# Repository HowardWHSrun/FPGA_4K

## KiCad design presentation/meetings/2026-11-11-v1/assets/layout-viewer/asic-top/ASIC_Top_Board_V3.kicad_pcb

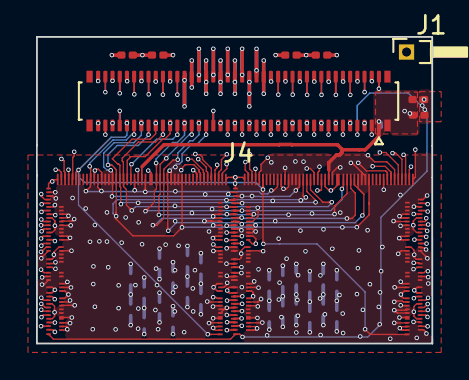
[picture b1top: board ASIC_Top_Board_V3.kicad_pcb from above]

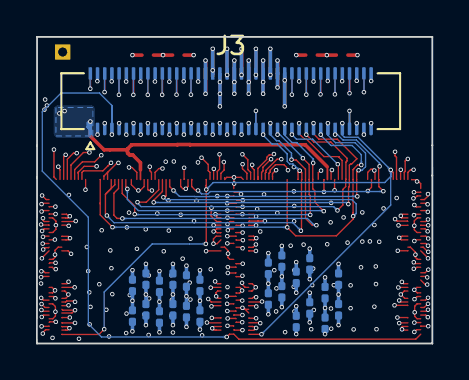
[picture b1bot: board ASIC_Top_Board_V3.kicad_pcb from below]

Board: 10 copper layers, 22.0 x 17.0 mm, 35 parts (25 on the bottom side), 78 nets.

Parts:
C1, C2, C4, C5, C6, C7, C14, C18, C19, C25, C26, C33, C34, C41, C42, C46, C48, C50, C51, C52, C53, C54, C55, C56, C57, C58, C59, C60, C61, C62: C_Small_US; C_0201_0603Metric
J1: Conn_01x01_Pin; PinHeader_1x01_P1.00mm_Horizontal
J3: Conn_02x40_Odd_Even; Hirose_DF40C-80DS-0.4V_2x40_P0.4mm
J4: Conn_02x40_Odd_Even; Hirose_DF40C-80DP-0.4V_2x40-1MP_P0.4mm
U01_BCD1, U01_BCD2: *; U01_BCD_OFF_CHIP

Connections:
/AC_IN: J3.69, J4.69, U01_BCD1.AC_IN, U01_BCD2.AC_IN
/AGND: C1.2, C2.2, C4.2, C5.2, C6.2, C18.2, C19.2, C25.2, C26.2, C33.2, C34.2, C41.2, C42.2, C46.2, C48.2, C50.2, C51.2, C52.2, C53.2, C54.2, C55.2, C56.2, C57.2, C58.2, C59.2, C60.2, J1.1 (Pin_1_1), J3.42, J3.44, J4.42, J4.44, U01_BCD1.AGND2, U01_BCD1.AGND_1, U01_BCD1.LAGND_1, U01_BCD1.LAGND_2, U01_BCD1.LAGND_3, U01_BCD1.LAGND_4, U01_BCD1.LAGND_5, U01_BCD1.LAGND_6, U01_BCD1.LAGND_7, U01_BCD1.LAGND_8, U01_BCD1.LAGND_9, U01_BCD1.LAGND_10, U01_BCD1.LAGND_11, U01_BCD1.LAGND_12, U01_BCD1.LAGND_13, U01_BCD1.LAGND_14, U01_BCD1.LAGND_15, U01_BCD1.LREF_GND1, U01_BCD1.LREF_GND2, U01_BCD1.LREF_GND3, U01_BCD1.LREF_GND4, U01_BCD1.RAGND_1, U01_BCD1.RAGND_2, U01_BCD1.RAGND_3, U01_BCD1.RAGND_4, U01_BCD1.RAGND_5, U01_BCD1.RAGND_6, U01_BCD1.RAGND_7, U01_BCD1.RAGND_8, U01_BCD1.RAGND_9, U01_BCD1.RAGND_10, U01_BCD1.RAGND_11, U01_BCD1.RAGND_12, U01_BCD1.RAGND_13, U01_BCD1.RAGND_14, U01_BCD1.RAGND_15, U01_BCD1.REF_1, U01_BCD1.REF_2, U01_BCD1.REF_3, U01_BCD1.REF_4, U01_BCD1.RREF_GND1, U01_BCD1.RREF_GND2, U01_BCD1.RREF_GND3, U01_BCD1.RREF_GND4, U01_BCD2.AGND2, U01_BCD2.AGND_1, U01_BCD2.LAGND_1, U01_BCD2.LAGND_2, U01_BCD2.LAGND_3, U01_BCD2.LAGND_4, U01_BCD2.LAGND_5, U01_BCD2.LAGND_6, U01_BCD2.LAGND_7, U01_BCD2.LAGND_8, U01_BCD2.LAGND_9, U01_BCD2.LAGND_10, U01_BCD2.LAGND_11, U01_BCD2.LAGND_12, U01_BCD2.LAGND_13, U01_BCD2.LAGND_14, U01_BCD2.LAGND_15, U01_BCD2.LREF_GND1, U01_BCD2.LREF_GND2, U01_BCD2.LREF_GND3, U01_BCD2.LREF_GND4, U01_BCD2.RAGND_1, U01_BCD2.RAGND_2, U01_BCD2.RAGND_3, U01_BCD2.RAGND_4, U01_BCD2.RAGND_5, U01_BCD2.RAGND_6, U01_BCD2.RAGND_7, U01_BCD2.RAGND_8, U01_BCD2.RAGND_9, U01_BCD2.RAGND_10, U01_BCD2.RAGND_11, U01_BCD2.RAGND_12, U01_BCD2.RAGND_13, U01_BCD2.RAGND_14, U01_BCD2.RAGND_15, U01_BCD2.REF_1, U01_BCD2.REF_2, U01_BCD2.REF_3, U01_BCD2.REF_4, U01_BCD2.RREF_GND1, U01_BCD2.RREF_GND2, U01_BCD2.RREF_GND3, U01_BCD2.RREF_GND4
/CHIP_RESET: J3.71, J4.71, U01_BCD1.RRST_DIGITAL, U01_BCD1.RST_DRIVER, U01_BCD2.RRST_DIGITAL, U01_BCD2.RST_DRIVER
/CLK32MHZ: J3.45, J4.45
/CLK32MHZ(2): J3.19, J4.19
/CLKH: J3.7, J4.7, U01_BCD1.CLKH, U01_BCD2.CLKH
/D<1>: J3.79, J4.79
/D<1>(2): J3.33, J4.33
/D<2>: J3.77, J4.77
/D<2>(2): J3.31, J4.31
/D<3>: J3.75, J4.75
/D<3>(2): J3.29, J4.29
/D<4>: J3.73, J4.73
/D<4>(2): J3.27, J4.27
/D<5>: J3.43, J4.43
/D<5>(2): J3.17, J4.17
/D<6>: J3.41, J4.41
/D<6>(2): J3.15, J4.15
/D<7>: J3.39, J4.39
/D<7>(2): J3.13, J4.13
/D<8>: J3.37, J4.37
/D<8>(2): J3.11, J4.11
/DGND: C7.2, C14.2, C61.2, C62.2, J3.46, J3.48, J4.46, J4.48, U01_BCD1.DGND1, U01_BCD1.DGND2, U01_BCD1.DGND3, U01_BCD1.DGND4, U01_BCD1.EN_LDO, U01_BCD1.LDGND_1, U01_BCD1.LDGND_2, U01_BCD1.LDGND_3, U01_BCD1.LDGND_4, U01_BCD1.LDGND_5, U01_BCD1.LDGND_6, U01_BCD1.LDGND_7, U01_BCD1.LDGND_8, U01_BCD1.LDGND_9, U01_BCD1.LDGND_10, U01_BCD1.LDGND_11, U01_BCD1.LDGND_12, U01_BCD1.LDGND_13, U01_BCD1.RDGND_1, U01_BCD1.RDGND_2, U01_BCD1.RDGND_3, U01_BCD1.RDGND_4, U01_BCD1.RDGND_5, U01_BCD1.RDGND_6, U01_BCD1.RDGND_7, U01_BCD1.RDGND_8, U01_BCD1.RDGND_9, U01_BCD1.RDGND_10, U01_BCD1.RDGND_11, U01_BCD1.RDGND_12, U01_BCD1.RDGND_13, U01_BCD2.DGND1, U01_BCD2.DGND2, U01_BCD2.DGND3, U01_BCD2.DGND4, U01_BCD2.EN_LDO, U01_BCD2.LDGND_1, U01_BCD2.LDGND_2, U01_BCD2.LDGND_3, U01_BCD2.LDGND_4, U01_BCD2.LDGND_5, U01_BCD2.LDGND_6, U01_BCD2.LDGND_7, U01_BCD2.LDGND_8, U01_BCD2.LDGND_9, U01_BCD2.LDGND_10, U01_BCD2.LDGND_11, U01_BCD2.LDGND_12, U01_BCD2.LDGND_13, U01_BCD2.RDGND_1, U01_BCD2.RDGND_2, U01_BCD2.RDGND_3, U01_BCD2.RDGND_4, U01_BCD2.RDGND_5, U01_BCD2.RDGND_6, U01_BCD2.RDGND_7, U01_BCD2.RDGND_8, U01_BCD2.RDGND_9, U01_BCD2.RDGND_10, U01_BCD2.RDGND_11, U01_BCD2.RDGND_12, U01_BCD2.RDGND_13
/DISC_OUT: J3.5, J4.5
/DISC_OUT(2): J3.3, J4.3
/DVDD: C7.1, C14.1, C61.1, C62.1, J3.34, J4.34, U01_BCD1.CGEN_RST, U01_BCD1.LDVDD_B1, U01_BCD1.LDVDD_B2, U01_BCD1.LDVDD_B3, U01_BCD1.LDVDD_T1, U01_BCD1.LDVDD_T2, U01_BCD1.LDVDD_T3, U01_BCD1.RDVDD_B1, U01_BCD1.RDVDD_B2, U01_BCD1.RDVDD_B3, U01_BCD1.RDVDD_T1, U01_BCD1.RDVDD_T2, U01_BCD1.RDVDD_T3, U01_BCD1.SPI_LDO_O, U01_BCD1.SPI_LDO_P, U01_BCD1.SPI_LDO_P1, U01_BCD1.SPI_LDO_P2, U01_BCD2.CGEN_RST, U01_BCD2.LDVDD_B1, U01_BCD2.LDVDD_B2, U01_BCD2.LDVDD_B3, U01_BCD2.LDVDD_T1, U01_BCD2.LDVDD_T2, U01_BCD2.LDVDD_T3, U01_BCD2.RDVDD_B1, U01_BCD2.RDVDD_B2, U01_BCD2.RDVDD_B3, U01_BCD2.RDVDD_T1, U01_BCD2.RDVDD_T2, U01_BCD2.RDVDD_T3, U01_BCD2.SPI_LDO_O, U01_BCD2.SPI_LDO_P, U01_BCD2.SPI_LDO_P1, U01_BCD2.SPI_LDO_P2
/FE_RESET: J3.65, J4.65, U01_BCD1.RST_FEL, U01_BCD1.RST_FER, U01_BCD2.RST_FEL, U01_BCD2.RST_FER
/IMP_TEST: J3.67, J4.67, U01_BCD1.IMP_TST, U01_BCD2.IMP_TST
/READ: J3.35, J4.35
/READ(2): J3.9, J4.9
/REF_VCM: C5.1, C46.1, C57.1, C58.1, J3.40, J4.40, U01_BCD1.LREF_VCM1, U01_BCD1.LREF_VCM2, U01_BCD1.LREF_VCM3, U01_BCD1.LREF_VCM4, U01_BCD1.RREF_VCM1, U01_BCD1.RREF_VCM2, U01_BCD1.RREF_VCM3, U01_BCD1.RREF_VCM4, U01_BCD1.VCM, U01_BCD2.LREF_VCM1, U01_BCD2.LREF_VCM2, U01_BCD2.LREF_VCM3, U01_BCD2.LREF_VCM4, U01_BCD2.RREF_VCM1, U01_BCD2.RREF_VCM2, U01_BCD2.RREF_VCM3, U01_BCD2.RREF_VCM4, U01_BCD2.VCM
/REF_VDD: C2.1, C33.1, C55.1, C56.1, J3.52, J4.52, U01_BCD1.LREF_VDD1, U01_BCD1.LREF_VDD2, U01_BCD1.LREF_VDD3, U01_BCD1.LREF_VDD4, U01_BCD1.RREF_VDD1, U01_BCD1.RREF_VDD2, U01_BCD1.RREF_VDD3, U01_BCD1.RREF_VDD4, U01_BCD2.LREF_VDD1, U01_BCD2.LREF_VDD2, U01_BCD2.LREF_VDD3, U01_BCD2.LREF_VDD4, U01_BCD2.RREF_VDD1, U01_BCD2.RREF_VDD2, U01_BCD2.RREF_VDD3, U01_BCD2.RREF_VDD4
/SPARE_P2: J3.2, J4.2
/SPARE_P4: J3.4, J4.4
/SPARE_P6: J3.6, J4.6
/SPARE_P8: J3.8, J4.8
/SPARE_P24: J3.24, J4.24
/SPARE_P58: J3.58, J4.58
/SPI_CLK: J3.63, J4.63, U01_BCD1.SPI_CLK, U01_BCD2.SPI_CLK
/SPI_DINL: J3.59, J4.59, U01_BCD1.SPI_DINL
/SPI_DINL(2): J3.25, J4.25, U01_BCD2.SPI_DINL
/SPI_DINR: J3.57, J4.57, U01_BCD1.SPI_DINR
/SPI_DINR(2): J3.23, J4.23, U01_BCD2.SPI_DINR
/SPI_LATCH: J3.61, J4.61, U01_BCD1.SPI_LATCH, U01_BCD2.SPI_LATCH
/STIM_CHB: J3.49, J4.49, U01_BCD1.FPGA_CHBL, U01_BCD1.FPGA_CHBR, U01_BCD2.FPGA_CHBL, U01_BCD2.FPGA_CHBR
/STIM_CLK: J3.53, J4.53, U01_BCD1.FPGA_CLK, U01_BCD2.FPGA_CLK
/STIM_EN: J3.51, J4.51, U01_BCD1.FPGA_EN, U01_BCD2.FPGA_EN
/STIM_START: J3.55, J4.55, U01_BCD1.FPGA_START, U01_BCD2.FPGA_START
/SYNC: J3.47, J4.47
/SYNC(2): J3.21, J4.21
/T_CLK32MHZ: J3.70, J4.70, U01_BCD1.CLK32MHZ
/T_CLK32MHZ(2): J3.20, J4.20, U01_BCD2.CLK32MHZ
/T_D<1>: J3.80, J4.80, U01_BCD1.DATAL<4>
/T_D<1>(2): J3.32, J4.32, U01_BCD2.DATAL<4>
/T_D<2>: J3.78, J4.78, U01_BCD1.DATAL<3>
/T_D<2>(2): J3.30, J4.30, U01_BCD2.DATAL<3>
/T_D<3>: J3.76, J4.76, U01_BCD1.DATAL<2>
/T_D<3>(2): J3.28, J4.28, U01_BCD2.DATAL<2>
/T_D<4>: J3.74, J4.74, U01_BCD1.DATAL<1>
/T_D<4>(2): J3.26, J4.26, U01_BCD2.DATAL<1>
/T_D<5>: J3.68, J4.68, U01_BCD1.DATAR<4>
/T_D<5>(2): J3.18, J4.18, U01_BCD2.DATAR<4>
/T_D<6>: J3.66, J4.66, U01_BCD1.DATAR<3>
/T_D<6>(2): J3.16, J4.16, U01_BCD2.DATAR<3>
/T_D<7>: J3.64, J4.64, U01_BCD1.DATAR<2>
/T_D<7>(2): J3.14, J4.14, U01_BCD2.DATAR<2>
/T_D<8>: J3.62, J4.62, U01_BCD1.DATAR<1>
/T_D<8>(2): J3.12, J4.12, U01_BCD2.DATAR<1>
/T_READ: J3.60, J4.60, U01_BCD1.READ
/T_READ(2): J3.10, J4.10, U01_BCD2.READ
/T_SYNC: J3.72, J4.72, U01_BCD1.SYNC
/T_SYNC(2): J3.22, J4.22, U01_BCD2.SYNC
/VDD10: C18.1, C19.1, J3.36, J4.36, U01_BCD1.P10_L, U01_BCD1.P10_R, U01_BCD2.P10_L, U01_BCD2.P10_R
/VDD_ADC: C1.1, C34.1, C53.1, C54.1, J3.56, J4.56, U01_BCD1.LVDD_ADC1, U01_BCD1.LVDD_ADC2, U01_BCD1.LVDD_ADC3, U01_BCD1.LVDD_ADC4, U01_BCD1.LVDD_ADC5, U01_BCD1.RVDD_ADC1, U01_BCD1.RVDD_ADC2, U01_BCD1.RVDD_ADC3, U01_BCD1.RVDD_ADC4, U01_BCD1.RVDD_ADC5, U01_BCD2.LVDD_ADC1, U01_BCD2.LVDD_ADC2, U01_BCD2.LVDD_ADC3, U01_BCD2.LVDD_ADC4, U01_BCD2.LVDD_ADC5, U01_BCD2.RVDD_ADC1, U01_BCD2.RVDD_ADC2, U01_BCD2.RVDD_ADC3, U01_BCD2.RVDD_ADC4, U01_BCD2.RVDD_ADC5
/VDD_CGEN: C6.1, C50.1, J3.1, J4.1, U01_BCD1.VDD_CGEN, U01_BCD2.VDD_CGEN
/VDD_DRIVER: C41.1, C42.1, C59.1, C60.1, J3.38, J4.38, U01_BCD1.LVDD_DRIVER1, U01_BCD1.LVDD_DRIVER2, U01_BCD1.LVDD_DRIVER3, U01_BCD1.LVDD_DRIVER4, U01_BCD1.LVDD_DRIVER5, U01_BCD1.RVDD_DRIVER1, U01_BCD1.RVDD_DRIVER2, U01_BCD1.RVDD_DRIVER3, U01_BCD1.RVDD_DRIVER4, U01_BCD1.RVDD_DRIVER5, U01_BCD2.LVDD_DRIVER1, U01_BCD2.LVDD_DRIVER2, U01_BCD2.LVDD_DRIVER3, U01_BCD2.LVDD_DRIVER4, U01_BCD2.LVDD_DRIVER5, U01_BCD2.RVDD_DRIVER1, U01_BCD2.RVDD_DRIVER2, U01_BCD2.RVDD_DRIVER3, U01_BCD2.RVDD_DRIVER4, U01_BCD2.RVDD_DRIVER5
/VDD_FE: C4.1, C48.1, C51.1, C52.1, J3.50, J4.50, U01_BCD1.LVDD_FE1, U01_BCD1.LVDD_FE2, U01_BCD1.LVDD_FE3, U01_BCD1.LVDD_FE4, U01_BCD1.RVDD_FE1, U01_BCD1.RVDD_FE2, U01_BCD1.RVDD_FE3, U01_BCD1.RVDD_FE4, U01_BCD2.LVDD_FE1, U01_BCD2.LVDD_FE2, U01_BCD2.LVDD_FE3, U01_BCD2.LVDD_FE4, U01_BCD2.RVDD_FE1, U01_BCD2.RVDD_FE2, U01_BCD2.RVDD_FE3, U01_BCD2.RVDD_FE4
/VSS10: C25.1, C26.1, J3.54, J4.54, U01_BCD1.M10_L, U01_BCD1.M10_R, U01_BCD2.M10_L, U01_BCD2.M10_R

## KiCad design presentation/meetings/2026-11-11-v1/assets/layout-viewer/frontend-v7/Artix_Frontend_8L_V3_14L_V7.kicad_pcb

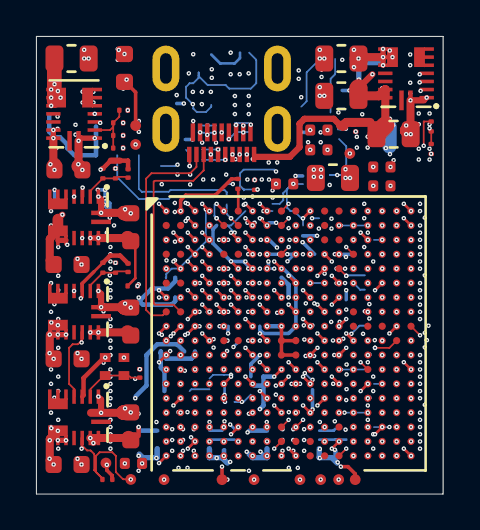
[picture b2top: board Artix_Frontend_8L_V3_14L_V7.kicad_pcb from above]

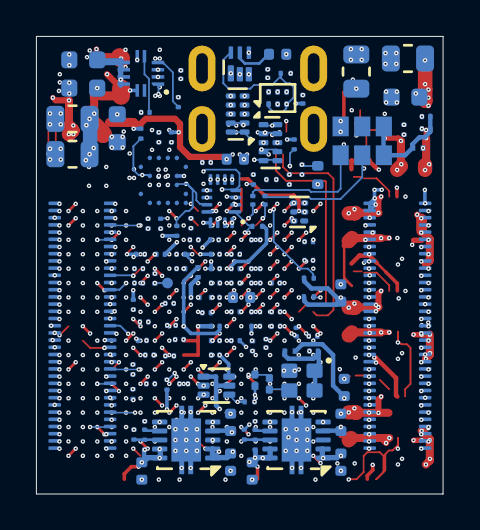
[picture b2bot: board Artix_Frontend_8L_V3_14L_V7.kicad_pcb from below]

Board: 14 copper layers, 22.6 x 25.4 mm, 185 parts (126 on the bottom side), 189 nets.

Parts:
C1, C2, C12, C13, C21, C22, C85, C86: 22uF; C_0603_1608Metric
C3, C14, C23, C87: 22pF; C_0201_GRM03_Murata_0p22Gap
C4, C89: 100uF; C_0805_2012Metric
C5, C6, C25, C36, C37, C51, C54, C96, C107: 4.7uF; C_0201_GRM03_Murata_0p22Gap
C7, C8, C9, C11, C18, C19, C20, C26, C27, C28, C29, C32, C33, C34, C35, C38, C39, C40, C52, C53, C55, C56, C57, C58, C80, C91, C92, C93, C97, C98, C99, C100: 470nF; C_0201_GRM03_Murata_0p22Gap
C10, C15, C42, C59: 47uF; C_0805_2012Metric
C16, C17, C24, C30, C31, C43, C44, C45, C47, C48, C49, C90, C94, C95, C101: 4.7uF; C_0402_1005Metric
C46, C50: 10nF; C_0201_GRM03_Murata_0p22Gap
C60, C63, C78, C79, C81, C82, C83, C88, C105, C106, C209: 100nF; C_0201_GRM03_Murata_0p22Gap
C61, C84: 1uF; C_0402_1005Metric
C62: 220nF; C_0201_GRM03_Murata_0p22Gap
C75, C76, C102, C104: 22uF / 6.3V; C_0603_1608Metric
C77: 22nF / 16V; C_0201_GRM03_Murata_0p22Gap
C103: 470nF / 6.3V; C_0201_GRM03_Murata_0p22Gap
C206, C207, C208: 22uF / 10V; C_0805_2012Metric
J1, J2: DF40C-70DS-0.4V(51); Hirose_DF40C-70DS-0.4V_2x35_P0.4mm
J3: Micro-HDMI 467651001; Molex_MicroHDMI_46765_1xxx
L1, L2, L3, L4: MPZ0603S121HT000; TDK_MPZ0603S121HT000_0201_Land_0p25x0p30_Gap0p30
R1, R4, R5, R41, R55, R59: 200k; R_0201_ERA1A_Panasonic_0p30Gap
R2: 301k; R_0201_ERA1A_Panasonic_0p30Gap
R3, R9, R11, R14, R17, R18, R19, R22, R38, R43, R58: 4.99k; R_0201_ERA1A_Panasonic_0p30Gap
R7: 150k; R_0402_TE_CPF_Reflow_0p50Gap
R8: 100k; R_0402_TE_CPF_Reflow_0p50Gap
R10: 1.3k; R_0201_ERA1A_Panasonic_0p30Gap
R13: 2.49k; R_0201_ERA1A_Panasonic_0p30Gap
R16, R61, R62, R64: 100R; R_0201_ERA1A_Panasonic_0p30Gap
R20, R21, R49, R50: 4.7k; R_0201_ERA1A_Panasonic_0p30Gap
R25: 470R; R_0201_ERA1A_Panasonic_0p30Gap
R27: 1k; R_0201_ERA1A_Panasonic_0p30Gap
R37: 24k / 1%; R_0201_ERA1A_Panasonic_0p30Gap
R42: 150k; R_0201_ERA1A_Panasonic_0p30Gap
R44: 150R; R_0201_0603Metric
R45: 4.64k; R_0402_1005Metric
R46, R47, R48, R57: 10k; R_0201_ERA1A_Panasonic_0p30Gap
R51, R52, R53: 47k; R_0201_ERA1A_Panasonic_0p30Gap
R54: 22k; R_0201_ERA1A_Panasonic_0p30Gap
R60: 44.2k; R_0201_ERA1A_Panasonic_0p30Gap
R63: 680R; R_0201_0603Metric
TP1, TP2, TP3, TP4, TP5, TP6, TP7, TP8, TP9, TP10, TP11, TP12, TP13, TP14: 0.6mm COPPER; TestPoint_Pad_D0.6mm_Edge_NoPaste
U1: XC7A35T-2CSG325C; Xilinx_CSG325
U2, U3, U4, U13, U16: MPM3833CGRH; MPS_QFN-18_2.5x3.5mm_MPM3833C
U5, U6: TPS74801DRCRM3; VSON-10-1EP_3x3mm_P0.5mm_EP1.65x2.4mm
U7: W25Q128JWYIQ; Winbond_WLCSP-21_P0.5mm
U8: SN74AVC4T774RSVR / SPI x1; TI_RSV_UQFN16_1.8x2.6mm_P0.4mm
U10: MP5077GG-Z; MPS_MP5077_QFN12_2x2mm_P0.4mm
U11: 74AUP2G07GM / dual reset OD; Nexperia_SOT886_XSON6_1x1.45mm
U12: TPS389001 / timed rail-ready reset; TI_DSE0006A_WSON6_1p5x1p5_P0p5_Manufacturer
U14: SN74AUP1G14 / SPI OE; Texas_USON-6_1x1.45mm_P0.5mm_SMD
U15: SN74AXC1T45DRLR; SOT-563
U17, U18: TPD4E02B04DQAR; USON-10_2.5x1.0mm_P0.5mm
Y1: AX3DAF1-125.0000T3 / 125 MHz; Abracon_AX3_3225_6pin
Y2: OT201625MJBA4SL / 25 MHz / 1.8 V; YXC_SMD2016-4P_2.0x1.6mm

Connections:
1V4_GTP_IN: C43.2, C47.2, C86.1, C87.1, R41.1, U5.1 (IN), U5.2 (IN), U6.1 (IN), U6.2 (IN), U13.3, U13.8, U13.9, U13.10
/ASIC1_CLK32MHz_Out: J2.59, U1.R2 (L13P_T2_MRCC)
/ASIC1_DATA1: J2.21, U1.U2 (L15P_T2_DQS)
/ASIC1_DATA2: J2.64, U1.J4 (L2N_T0)
/ASIC1_DATA3: J2.62, U1.K2 (L3P_T0_DQS)
/ASIC1_DATA4: J2.60, U1.K1 (L3N_T0_DQS)
/ASIC1_DATA5: J2.57, U1.M1 (L7N_T1)
/ASIC1_DATA6: J2.55, U1.N1 (L9P_T1_DQS)
/ASIC1_DATA7: J2.53, U1.P1 (L9N_T1_DQS)
/ASIC1_DATA8: J2.51, U1.L3 (L5N_T0)
/ASIC1_READ: J2.49, U1.L2 (L4N_T0)
/ASIC1_SYNC: J2.61, U1.J5 (L2P_T0)
/ASIC2_CLK32MHz_Out: J1.63, U1.D13 (L11P_T1_SRCC)
/ASIC2_DATA1: J1.70, U1.A17 (L15N_T2_DQS_ADV_B)
/ASIC2_DATA2: J1.51, U1.E15 (L13P_T2_MRCC)
/ASIC2_DATA3: J1.53, U1.D16 (L14N_T2_SRCC)
/ASIC2_DATA4: J1.55, U1.D15 (L13N_T2_MRCC)
/ASIC2_DATA5: J1.65, U1.B14 (L10P_T1_AD11P)
/ASIC2_DATA6: J1.67, U1.A15 (L10N_T1_AD11N)
/ASIC2_DATA7: J1.69, U1.A14 (L8N_T1_AD10N)
/ASIC2_DATA8: J1.38, U1.H17 (L23P_T3_FOE_B)
/ASIC2_READ: J1.40, U1.H18 (L23N_T3_FWE_B)
/ASIC2_SYNC: J1.61, U1.B15 (L9N_T1_DQS_AD3N)
/ASIC3_4_TOP_SPI_CLK: J2.37, U1.P3 (L12N_T1_MRCC)
/ASIC3_4_TOP_SPI_LATCH: J2.35, U1.R7 (L22P_T3)
/ASIC3_CLK32MHz_Out: J2.25, U1.P4 (L12P_T1_MRCC)
/ASIC3_DATA1: J2.47, U1.L5 (L6P_T0)
/ASIC3_DATA2: J2.45, U1.M6 (L8P_T1)
/ASIC3_DATA3: J2.43, U1.N2 (L11N_T1_SRCC)
/ASIC3_DATA4: J2.39, U1.N6 (L8N_T1)
/ASIC3_DATA5: J2.23, U1.T2 (L14N_T2_SRCC)
/ASIC3_DATA6: J2.42, U1.D9 (L2P_T0_AD8P)
/ASIC3_DATA7: J1.39, U1.D14 (L12N_T1_MRCC)
/ASIC3_DATA8: J1.43, U1.G15 (L21P_T3_DQS)
/ASIC3_READ: J1.45, U1.F14 (L22N_T3_A16)
/ASIC3_SPI_DL: J2.33, U1.R5 (L21P_T3_DQS)
/ASIC3_SPI_DR: J2.31, U1.T7 (L22N_T3)
/ASIC3_SYNC: J2.29, U1.T3 (L17N_T2)
/ASIC4_CLK32MHz_Out: J1.56, U1.E16 (L14P_T2_SRCC)
/ASIC4_DATA1: J1.47, U1.F15 (L21N_T3_DQS_A18)
/ASIC4_DATA2: J1.49, U1.E13 (L12P_T1_MRCC)
/ASIC4_DATA3: J1.44, U1.G17 (L19P_T3_A22)
/ASIC4_DATA4: J1.46, U1.F17 (L24P_T3_RS1)
/ASIC4_DATA5: J1.58, U1.D18 (L17N_T2_A25)
/ASIC4_DATA6: J1.60, U1.C18 (L18N_T2_A23)
/ASIC4_DATA7: J1.62, U1.C17 (L18P_T2_A24)
/ASIC4_DATA8: J1.64, U1.B17 (L16N_T2_A27)
/ASIC4_READ: J1.68, U1.B16 (L15P_T2_DQS)
/ASIC4_SPI_DL: J1.48, U1.F18 (L19N_T3_A21_VREF)
/ASIC4_SPI_DR: J1.52, U1.E18 (L24N_T3_RS0)
/ASIC4_SYNC: J1.54, U1.E17 (L17P_T2_A26)
/ASIC5_CLK32MHz_Out: J2.12, U1.R3 (L14P_T2_SRCC)
/ASIC5_DATA1: J2.5, U1.V4 (L18N_T2)
/ASIC5_DATA2: J2.7, U1.U1 (L15N_T2_DQS)
/ASIC5_DATA3: J2.9, U1.U4 (L18P_T2)
/ASIC5_DATA4: J2.11, U1.U5 (L20N_T3)
/ASIC5_DATA5: J2.10, U1.T5 (L21N_T3_DQS)
/ASIC5_DATA6: J2.8, U1.T4 (L17P_T2)
/ASIC5_DATA7: J2.6, U1.U6 (L20P_T3)
/ASIC5_DATA8: J2.4, U1.U7 (L23P_T3)
/ASIC5_READ: J2.2, U1.V3 (L16P_T2)
/ASIC5_SYNC: J2.3, U1.V2 (L16N_T2)
/ASIC6_CLK32MHz_Out: J1.16, U1.R16 (L14P_T2_SRCC)
/ASIC6_DATA1: J1.1, U1.V16 (L18P_T2_A12_D28)
/ASIC6_DATA2: J1.28, U1.K18 (L3N_T0_DQS_EMCCLK)
/ASIC6_DATA3: J1.26, U1.L18 (L4N_T0_D05)
/ASIC6_DATA4: J1.24, U1.M17 (L7N_T1_D10)
/ASIC6_DATA5: J1.12, U1.R18 (L15P_T2_DQS_RDWR_B)
/ASIC6_DATA6: J1.10, U1.R17 (L14N_T2_SRCC)
/ASIC6_DATA7: J1.8, U1.T18 (L15N_T2_DQS_DOUT_CSO_B)
/ASIC6_DATA8: J1.6, U1.T17 (L16P_T2_CSI_B)
/ASIC6_READ: J1.4, U1.U17 (L16N_T2_A15_D31)
/ASIC6_SYNC: J1.18, U1.P18 (L10N_T1_D15)
/ASIC7_8_TOP_SPI_CLK: J2.24, U1.N4 (L10N_T1)
/ASIC7_8_TOP_SPI_LATCH: J2.26, U1.L4 (L5P_T0)
/ASIC7_CLK32MHz_Out: J2.36, U1.N3 (L11P_T1_SRCC)
/ASIC7_DATA1: J2.16, U1.R1 (L13N_T2_MRCC)
/ASIC7_DATA2: J2.18, U1.R6 (IO25)
/ASIC7_DATA3: J2.20, U1.P5 (L19N_T3_VREF)
/ASIC7_DATA4: J2.22, U1.P6 (L19P_T3)
/ASIC7_DATA5: J2.38, U1.K3 (L4P_T0)
/ASIC7_DATA6: J2.40, U1.U9 (L24P_T3_A01_D17)
/ASIC7_DATA7: J1.37, U1.H16 (L20P_T3_A20)
/ASIC7_DATA8: J1.35, U1.V13 (L21N_T3_DQS_A06_D22)
/ASIC7_READ: J1.33, U1.T12 (L22P_T3_A05_D21)
/ASIC7_SPI_DL: J2.28, U1.M4 (L10P_T1)
/ASIC7_SPI_DR: J2.30, U1.M2 (L7P_T1)
/ASIC7_SYNC: J2.32, U1.M5 (L6N_T0_VREF)
/ASIC8_CLK32MHz_Out: J1.13, U1.P15 (L11P_T1_SRCC)
/ASIC8_DATA1: J1.31, U1.U12 (L22N_T3_A04_D20)
/ASIC8_DATA2: J1.29, U1.K17 (L4P_T0_D04)
/ASIC8_DATA3: J1.25, U1.K15 (L5N_T0_D07)
/ASIC8_DATA4: J1.23, U1.L14 (IO0)
/ASIC8_DATA5: J1.11, U1.R13 (L19P_T3_A10_D26)
/ASIC8_DATA6: J1.9, U1.T15 (L13N_T2_MRCC)
/ASIC8_DATA7: J1.7, U1.U14 (L20P_T3_A08_D24)
/ASIC8_DATA8: J1.5, U1.U16 (L17N_T2_A13_D29)
/ASIC8_READ: J1.3, U1.U15 (L17P_T2_A14_D30)
/ASIC8_SPI_DL: J1.21, U1.M16 (L7P_T1_D09)
/ASIC8_SPI_DR: J1.19, U1.N16 (L9P_T1_DQS)
/ASIC8_SYNC: J1.17, U1.P16 (L11N_T1_SRCC)
/CABLE_CLK_N: J3.8 (TX1_REC_N), R61.2, U1.R15 (L12N_T1_MRCC), U17.2, U17.9
/CABLE_CLK_P: J3.6 (TX1_REC_P), R61.1, U1.P14 (L12P_T1_MRCC), U17.1, U17.10
/CABLE_CMDSYNC_N: J3.11 (TX2_REC_N), R62.2, U1.N14 (L8N_T1_D12), U17.5, U17.6
/CABLE_CMDSYNC_P: J3.9 (TX2_REC_P), R62.1, U1.M14 (L8P_T1_D11), U17.4, U17.7
/CABLE_SYNC_N: J3.14 (GPIO_CMD_N), R64.2, U1.A9 (L3N_T0_DQS_AD1N), U18.2, U18.9
/CABLE_SYNC_P: J3.12 (GPIO_CMD_P), R64.1, U1.B9 (L3P_T0_DQS_AD1P), U18.1, U18.10
/CLK25_RAW: R44.1, Y2.3
/CLK25_VDD: C88.1, L3.2, Y2.1, Y2.4
/FB_GTP_1V4: C87.2, R41.2, R42.1, U13.2
/FB_VIN_3V3: R59.2, R60.1, U16.2
/FE_RESET_SHARED: J2.54, U1.D8 (L1P_T0_AD0P)
/IMP_TST_SHARED: J2.56, U1.C8 (L1N_T0_AD0N)
/SPARE_J1_36: J1.36, U1.V14 (L20N_T3_A07_D23)
/STIM_CHIP1_SPI_DL: J2.46, U1.C11 (L4P_T0)
/STIM_CHIP1_SPI_DR: J2.44, U1.G14 (L22P_T3_A17)
/STIM_CHIP2_SPI_DL: J1.57, U1.C14 (L9P_T1_DQS_AD3P)
/STIM_CHIP3_SPI_DL: J2.17, U1.V7 (L24N_T3)
/STIM_CHIP4_SPI_DR: J1.20, U1.N18 (L10P_T1_D14)
BOARD1_CLK: J1.42, U1.G16 (L20N_T3_A19)
BOARD1_SPI_CLK: J2.52, U1.D10 (IO0)
BOARD3_CLK: J1.2, U1.V17 (L18N_T2_A11_D27)
BOARD3_SPI_CLK: J2.13, U1.V8 (L24P_T3)
BOOT_RAILS_PG_3V3: R9.2, TP10.1 (PAD_1), U4.12, U5.3 (PG), U6.5 (EN), U12.3 (MR_PG)
BOOT_RESET_N: R47.2, U11.1 (1A_RESET_N), U11.3 (2A_RESET_N), U12.6 (RESET_N_OD), U14.2
CABLE_TARGET_SENSE: J3.1 (SENSE), R27.2
CHIP_RESET_SHARED: J2.58, U1.C9 (L2N_T0_AD8N)
CLK25_PL: R44.2, R63.1, U1.T14 (L13P_T2_MRCC)
EN_GTPWR_1V5: R58.2, U1.M15 (L6N_T0_D08_VREF), U15.3
EN_GTPWR_3V3: R57.1, U13.4, U15.4
FLASH_CS_N_1V8: R22.2, U7.1, U8.11 (B2_CS)
FLASH_DQ0_1V8: R53.2, U7.5, U8.10 (B3_MOSI)
FLASH_DQ1_1V8: R51.1, U7.2, U8.9 (B4_MISO)
FLASH_HOLD_N_1V8: R21.2, U7.7
FLASH_READY_SENSE: R45.2, R46.1, U12.1 (SENSE_DIV)
FLASH_SCK_1V8: R52.1, U7.6, U8.12 (B1_SCK)
FLASH_TRANSLATOR_OE_N: R48.2, U8.7 (OE_N), U14.4
FLASH_WP_N_1V8: R20.2, U7.3
FPGA_DONE: R38.2, TP12.1 (PAD_1), U1.F12 (DONE_0)
FPGA_INIT_B: R18.2, TP11.1 (PAD_1), U1.T10 (INIT_B_0), U11.4 (2Y_INIT_OD)
FPGA_JTAG_TCK: J3.17 (TCK), U1.F8 (TCK_0)
FPGA_JTAG_TDI: J3.15 (TDI), U1.T9 (TDI_0)
FPGA_JTAG_TDO: J3.18 (TDO), U1.T8 (TDO_0)
FPGA_JTAG_TMS: J3.2 (TMS), U1.R8 (TMS_0)
FPGA_PROGRAM_B: R17.2, U1.P10 (PROGRAM_B_0), U11.6 (1Y_PROGRAM_OD)
FPGA_PUDC_B: R25.2, U1.J18 (L3P_T0_DQS_PUDC_B)
FPGA_QSPI_CCLK: R49.2, U1.E8 (CCLK_0), U8.1 (A1_CCLK)
FPGA_QSPI_CS_N: R19.2, U1.L15 (L6P_T0_FCS_B), U8.2 (A2_CS)
FPGA_QSPI_DQ0: R50.2, U1.K16 (L1P_T0_D00_MOSI), U8.3 (A3_MOSI)
FPGA_QSPI_DQ1: R54.1, U1.L17 (L1N_T0_D01_DIN), U8.4 (A4_MISO)
GND: C1.2, C2.2, C4.2, C5.2, C6.2, C7.2, C8.2, C9.2, C10.2, C11.2, C12.2, C13.2, C15.2, C16.2, C17.2, C18.2, C19.2, C20.2, C21.2, C22.2, C24.2, C25.2, C26.2, C27.2, C28.2, C29.2, C30.2, C31.2, C32.2, C33.2, C34.2, C35.2, C36.2, C37.2, C38.2, C39.2, C40.2, C42.2, C43.1, C44.2, C45.2, C46.2, C47.1, C48.2, C49.2, C50.2, C51.2, C52.2, C53.2, C54.2, C55.2, C56.2, C58.2, C59.2, C60.2, C61.2, C62.2, C63.2, C75.2, C76.2, C77.2, C80.2, C81.2, C82.2, C83.2, C84.2, C85.2, C86.2, C88.2, C89.2, C90.2, C91.2, C92.2, C93.2, C94.2, C95.2, C96.2, C97.2, C98.2, C99.2, C100.2, C101.2, C102.2, C103.2, C104.2, C105.2, C106.2, C107.2, C206.2, C207.2, C208.2, C209.2, J1.14, J1.15, J1.27, J1.30, J1.34, J1.41, J1.50, J1.66, J2.14, J2.15, J2.27, J2.34, J2.41, J2.50, J2.66, J3.4 (GND), J3.7 (GND), J3.10 (GND), J3.13 (GND), J3.16 (GND), J3.SH (SHIELD), L2.1, R2.2, R5.2, R8.2, R11.2, R14.2, R37.2, R42.2, R46.2, R51.2, R52.2, R54.2, R55.2, R57.2, R60.2, R63.2, TP1.1 (PAD_1), TP13.1 (PAD_1), U1.A1 (GND_[75_balls]), U1.A3 (MGTPRXN1_216), U1.A4 (MGTPRXP1_216), U1.A5 (GND), U1.A7 (GND), U1.A8 (GND), U1.A11 (GND), U1.A18 (GND), U1.B3 (GND), U1.B7 (GND), U1.B8 (GND), U1.B18 (GND), U1.C2 (GND), U1.C3 (MGTPRXN2_216), U1.C4 (MGTPRXP2_216), U1.C6 (GND), U1.C7 (GND), U1.C15 (GND), U1.D3 (GND), U1.D4 (GND), U1.D7 (GND), U1.D12 (GND), U1.E2 (GND), U1.E3 (MGTPRXN0_216), U1.E4 (MGTPRXP0_216), U1.E6 (GND), U1.E7 (GND), U1.E9 (GND), U1.E12 (CFGBVS_0), U1.F4 (GND), U1.F6 (GND), U1.F10 (GND), U1.F13 (M2_0), U1.F16 (GND), U1.G1 (GND), U1.G3 (MGTPRXN3_216), U1.G4 (MGTPRXP3_216), U1.G5 (GND), U1.G6 (GND), U1.G7 (GND), U1.G9 (GND), U1.G11 (GND), U1.G13 (GND), U1.H3 (GND), U1.H4 (GND), U1.H5 (GND), U1.H6 (GND), U1.H8 (GND), U1.H10 (GND), U1.H12 (GND), U1.J1 (GND), U1.J2 (GND), U1.J3 (GND), U1.J7 (GND), U1.J11 (GND), U1.J13 (GND), U1.J17 (GND), U1.K4 (GND), U1.K8 (GND), U1.K12 (GND), U1.K14 (GND), U1.L1 (GND), U1.L7 (GND), U1.L11 (GND), U1.L13 (GND), U1.M8 (GND), U1.M9 (DXN_0), U1.M10 (DXP_0), U1.M12 (GND), U1.M18 (GND), U1.N5 (GND), U1.N7 (GND), U1.N9 (GND), U1.N11 (GND), U1.N13 (GND), U1.N15 (GND), U1.P2 (GND), U1.P8 (GND), U1.P12 (GND), U1.R9 (GND), U1.R11 (M1_0), U1.T6 (GND), U1.T16 (GND), U1.U3 (GND), U1.U13 (GND), U1.V1 (GND), U1.V10 (GND), U1.V18 (GND), U2.1, U2.16, U3.1, U3.16, U4.1, U4.16, U5.6 (GND), U5.11 (GND_EP), U6.6 (GND), U6.11 (GND_EP), U7.4, U8.6 (DIR4_L), U8.8 (GND), U10.2 (GND), U11.2 (GND), U12.2 (GND), U13.1, U13.16, U14.3, U15.2, U16.1, U16.16, U17.3, U17.8, U18.3, U18.4, U18.5, U18.6, U18.7, U18.8, Y1.3 (GND), Y2.2
GNDADC_XADC: C57.2, L2.2, U1.J9 (GNDADC_0), U1.K9 (VREFN_0), U1.K10 (VP_0), U1.L9 (VN_0), U1.L10 (VREFP_0)
GTP_REFCLK1_N: C79.2, U1.B5 (MGTREFCLK1N_216)
GTP_REFCLK1_P: C78.2, U1.B6 (MGTREFCLK1P_216)
GTP_TX0_N: J3.3 (TX0_REC_P), U1.H1 (MGTPTXN0_216)
GTP_TX0_P: J3.5 (TX0_REC_N), U1.H2 (MGTPTXP0_216)
MGTAVCC_1V0: C45.1, C51.1, C52.1, C53.1, R10.1, TP7.1 (PAD_1), U1.B4 (MGTAVCC), U1.C5 (MGTAVCC), U1.E5 (MGTAVCC), U1.F5 (MGTAVCC), U5.9 (OUT), U5.10 (OUT)
MGTAVTT_1V2: C49.1, C54.1, C55.1, C56.1, R13.1, R16.1, TP8.1 (PAD_1), U1.A2 (MGTAVTT), U1.C1 (MGTAVTT), U1.E1 (MGTAVTT), U1.F3 (MGTAVTT), U1.G2 (MGTAVTT), U6.9 (OUT), U6.10 (OUT)
unnamed: R16.2, U1.A6 (MGTRREF_216)
unnamed: C3.2, R1.2, R2.1, U2.2
unnamed: C14.2, R4.2, R5.1, R55.1, U3.2
unnamed: C23.2, R7.2, R8.1, U4.2
unnamed: R10.2, R11.1, U5.8 (FB)
unnamed: C46.1, U5.7 (SS)
unnamed: R13.2, R14.1, U6.8 (FB)
unnamed: C50.1, U6.7 (SS)
unnamed: R37.1, U10.4 (ILIM)
unnamed: C77.1, U10.5 (SS)
unnamed: C84.1, U12.5 (CT)
OSC125_3V3: C80.1, C81.1, L4.2, Y1.1 (OE), Y1.6 (VDD)
OSC125_N: C79.1, Y1.5 (OUTN)
OSC125_P: C78.1, Y1.4 (OUTP)
PG_CORE_1V0: R3.2, U2.12, U3.4, U4.4, U10.1 (EN)
PG_GTP_1V4: R43.2, U5.5 (EN), U13.12
SPI_LATCH_SHARED: J2.48, U1.D11 (L6P_T0)
STIM_CHB_SHARED: J2.1, U1.V9 (L24N_T3_A00_D16)
STIM_CHIP2_SPI_DR: J1.59, U1.C16 (L16P_T2_A28)
STIM_CHIP3_SPI_DR: J2.19, U1.V6 (L23N_T3)
STIM_CHIP4_SPI_DL: J1.22, U1.N17 (L9N_T1_DQS_D13)
STIM_CLK_SHARED: J2.65, U1.B11 (L4N_T0)
STIM_EN_SHARED: J2.63, U1.J6 (IO0)
STIM_START_SHARED: J2.67, U1.B10 (L5P_T0_AD9P)
SWITCHED_3V3: C76.1, C104.1, C106.1, L4.1, TP3.1 (PAD_1), U10.7 (VOUT), U10.8 (VOUT), U10.9 (VOUT), U10.10 (VOUT), U15.6
VCCADC_1V8: C57.1, L1.2, U1.J10 (VCCADC_0)
VCCAUX_1V8: C13.1, C14.1, C15.1, C16.1, C17.1, C18.1, C19.1, C20.1, C58.1, C59.1, C60.1, C62.1, C94.1, C95.1, C96.1, C97.1, C98.1, C99.1, C100.1, L1.1, L3.1, R4.1, R17.1, R18.1, R20.1, R21.1, R22.1, R27.1, R38.1, R45.1, R49.1, R53.1, TP5.1 (PAD_1), TP9.1 (PAD_1), U1.E10 (VCCO_0), U1.E11 (VCCBATT_0), U1.G12 (VCCAUX_[5_balls]), U1.H13 (VCCAUX), U1.K13 (VCCAUX), U1.M13 (VCCAUX), U1.P13 (VCCAUX), U1.R10 (VCCO_0), U1.R12 (M0_0), U3.3, U3.8, U3.9, U3.10, U7.8, U8.13 (VCCB_1V8)
VCCINT_1V0: C2.1, C3.1, C4.1, C5.1, C6.1, C7.1, C8.1, C9.1, C10.1, C11.1, C89.1, C90.1, C91.1, C92.1, C93.1, R1.1, TP4.1 (PAD_1), U1.F7 (VCCINT_1V0), U1.F9 (VCCINT_1V0), U1.F11 (VCCBRAM/VCCINT_[21_balls]), U1.G8 (VCCINT_1V0), U1.G10 (VCCBRAM_1V0), U1.H7 (VCCINT_1V0), U1.H9 (VCCINT_1V0), U1.H11 (VCCBRAM_1V0), U1.J8 (VCCINT_1V0), U1.J12 (VCCINT_1V0), U1.K7 (VCCINT_1V0), U1.K11 (VCCINT_1V0), U1.L8 (VCCINT_1V0), U1.L12 (VCCINT_1V0), U1.M7 (VCCINT_1V0), U1.M11 (VCCINT_1V0), U1.N8 (VCCINT_1V0), U1.N10 (VCCINT_1V0), U1.N12 (VCCINT_1V0), U1.P9 (VCCINT_1V0), U1.P11 (VCCINT_1V0), U2.3, U2.8, U2.9, U2.10
VCCO_1V5: C22.1, C23.1, C24.1, C25.1, C26.1, C27.1, C28.1, C29.1, C30.1, C31.1, C32.1, C33.1, C34.1, C35.1, C36.1, C37.1, C38.1, C39.1, C40.1, C42.1, C61.1, C63.1, C101.1, C105.1, C107.1, R7.1, R19.1, R25.1, R48.1, R50.1, R58.1, TP6.1 (PAD_1), U1.A16 (VCCO), U1.B13 (VCCO), U1.C10 (VCCO), U1.D17 (VCCO), U1.E14 (VCCO), U1.G18 (VCCO), U1.H15 (VCCO), U1.L6 (VCCO), U1.L16 (VCCO), U1.M3 (VCCO), U1.P7 (VCCO), U1.P17 (VCCO), U1.R4 (VCCO), U1.R14 (VCCO), U1.T1 (VCCO), U1.T11 (VCCO), U1.U8 (VCCO), U1.U18 (VCCO), U1.V5 (VCCO), U1.V15 (VCCO), U4.3, U4.8, U4.9, U4.10, U8.5 (DIR3_H), U8.14 (VCCA_1V5), U8.15 (DIR1_H), U8.16 (DIR2_H), U14.6, U15.1, U15.5
VIN_3V3: C1.1, C12.1, C21.1, C44.1, C48.1, C75.1, C82.1, C83.1, C85.1, C102.1, C103.1, C208.1, J2.68, J2.69, J2.70, R3.1, R9.1, R43.1, R47.1, R59.1, TP2.1 (PAD_1), U2.4, U2.13, U2.14, U3.13, U3.14, U4.13, U4.14, U5.4 (BIAS), U6.4 (BIAS), U10.3 (VCC), U10.6 (VIN), U10.11 (VIN), U11.5 (VCC_3V3), U12.4 (VDD_3V3), U13.13, U13.14, U16.3, U16.8, U16.9, U16.10
VIN_5V: C206.1, C207.1, C209.1, J1.32, J3.19 (5V_IN), TP14.1 (PAD_1), U16.4, U16.13, U16.14
